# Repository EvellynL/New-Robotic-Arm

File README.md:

# 🦾Novo Braço Robótico - STEM CRIAR

O Novo Braço Robótico – STEM CRIAR é um projeto desenvolvido no âmbito do projeto STEM CRIAR. Este repositório reúne os códigos-fonte, bibliotecas, configurações e demais arquivos utilizados no desenvolvimento e controle do braço robótico.

## 💻Programação

Toda programação foi desenvolvida em C++ utilizando a plataforma **Visual Studio Code** juntamente com a extensão **PlatformIO (3.3.4)**. O projeto foi criado utilizando servos inteligentes da **Hiwonder** que contam driver, motor e circuito de controle de barramento. Os usuários podem enviar comandos específicos ao servomotor — com base no protocolo de comunicação fornecido pela nossa empresa — para controlar a rotação, ler informações do dispositivo ou alternar para o modo de motor de passo. Cada servomotor possui três interfaces, permitindo a conexão em cascata.

Link com mais informações sobre os servos inteligentes: https://drive.google.com/drive/folders/1yaZ8iRYgWncdHPopioo7OYuHoGhrMxCi?hl=pt-br <br>
Manual de configuração dos servos LX-15D também se encontra em: [eletronica](eletronica/LX_15D_Bus_Servo_User_Manual.pdf)

## ⚡Eletrônica

### 📍Componentes utilizados: 
- Servos LX-15D
- Serial Bus Servo Controller LBSC - V1.5
- ESP32 WROOM 32D
- Regulador de Tensão LM2596 ajustável com display
- Bateria 9v

### 📍Diagrama Elétrico: 

Link sobre informações da placa Serial Bus Servo Controller LBSC - V1.5 e configurar os ID's dos servos: https://docs.hiwonder.com/projects/Bus-Servo-Controller/en/latest/docs/1.Bus_Servo_Controller_User_Manual.html

## ⚙️Mecânica

Toda estrutura mecânica foi modelada e desenvolvida utilizando o software Inventor Autodesk na versão 2027 e se encontram na pasta: [Mecânica](mecanica/partes_ipt)

A fabricação das peças foram feitas nas impressoras 3D da Bambu Lab do modelo P1S utilizando filemanto PLA.

MAIS DETALHES EM ANDAMENTO....🚧🚧🚧

## ⚠️Observações:
- A tensão de operação dos Servos LX-15D está entre 6v - 8.4v. Valores menores impediram o funcionamento e valores maiores danificaram o componente.
- O ESP32 não controla os servos diretamente; ele se comunica com a placa Serial Bus Servo Controller por meio de uma interface serial UART. Portanto, a interface UART utilizada para a comunicação com a placa **não deve ser compartilhada com o Monitor Serial**, sendo recomendável utilizar interfaces seriais distintas para cada finalidade.
- Os Servos só funcionaram se estiverem pré-definidos com o seus ID's.
- Ao configurar os IDs dos servos utilizando o software da HiWonder, é possível que, em algumas placas controladoras, a porta de comunicação não seja identificada como uma porta COM no Windows, mas apareça no Gerenciador de Dispositivos como um dispositivo na categoria Human Interface Devices (HID). Isso ocorre porque, nesse caso, a comunicação com a placa é estabelecida por meio da **interface Wire**. Para verificar se a conexão foi reconhecida corretamente, basta consultar o status de “Wire Connect” no software da HiWonder.

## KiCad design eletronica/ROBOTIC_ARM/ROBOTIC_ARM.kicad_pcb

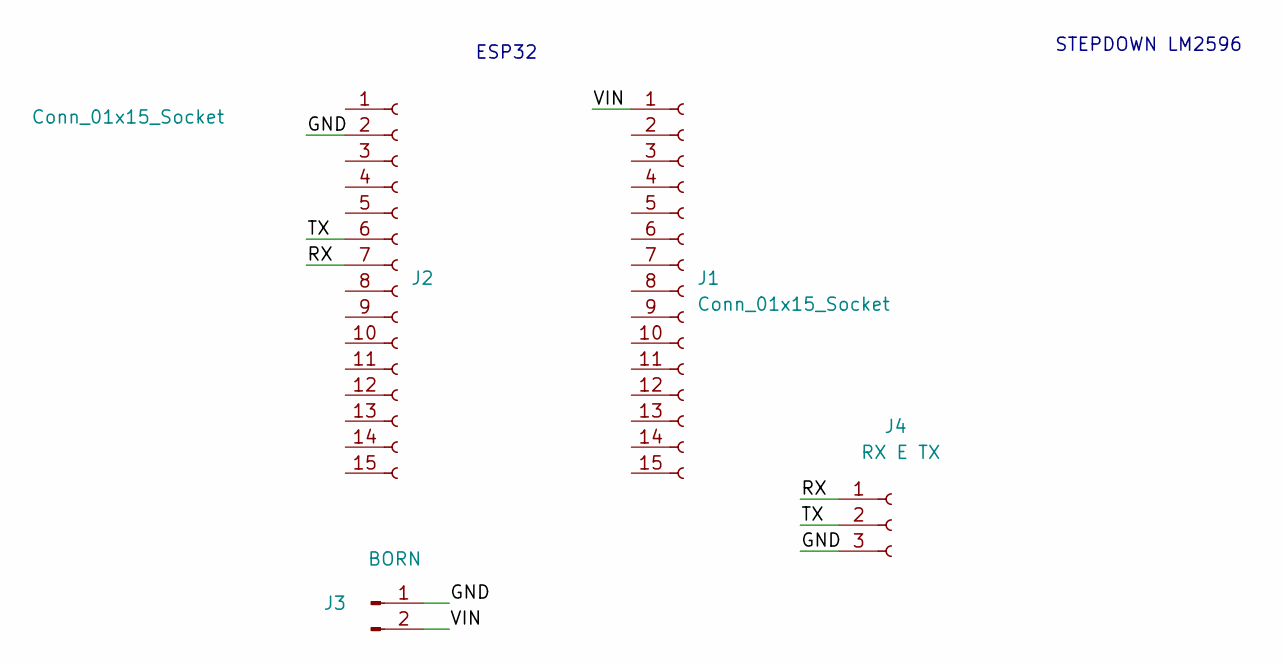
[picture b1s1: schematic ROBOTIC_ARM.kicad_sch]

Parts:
J1, J2: Conn_01x15_Socket; PinSocket_1x15_P2.54mm_Vertical
J3: BORN; TerminalBlock_Phoenix_MKDS-1,5-2_1x02_P5.00mm_Horizontal
J4: RX E TX; PinSocket_1x03_P2.54mm_Vertical

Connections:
/GND: J2.2, J3.1, J4.3
/RX: J2.7, J4.1
/TX: J2.6, J4.2
/VIN: J1.1 (Pin_1_1), J3.2

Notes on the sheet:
STEPDOWN LM2596
ESP32

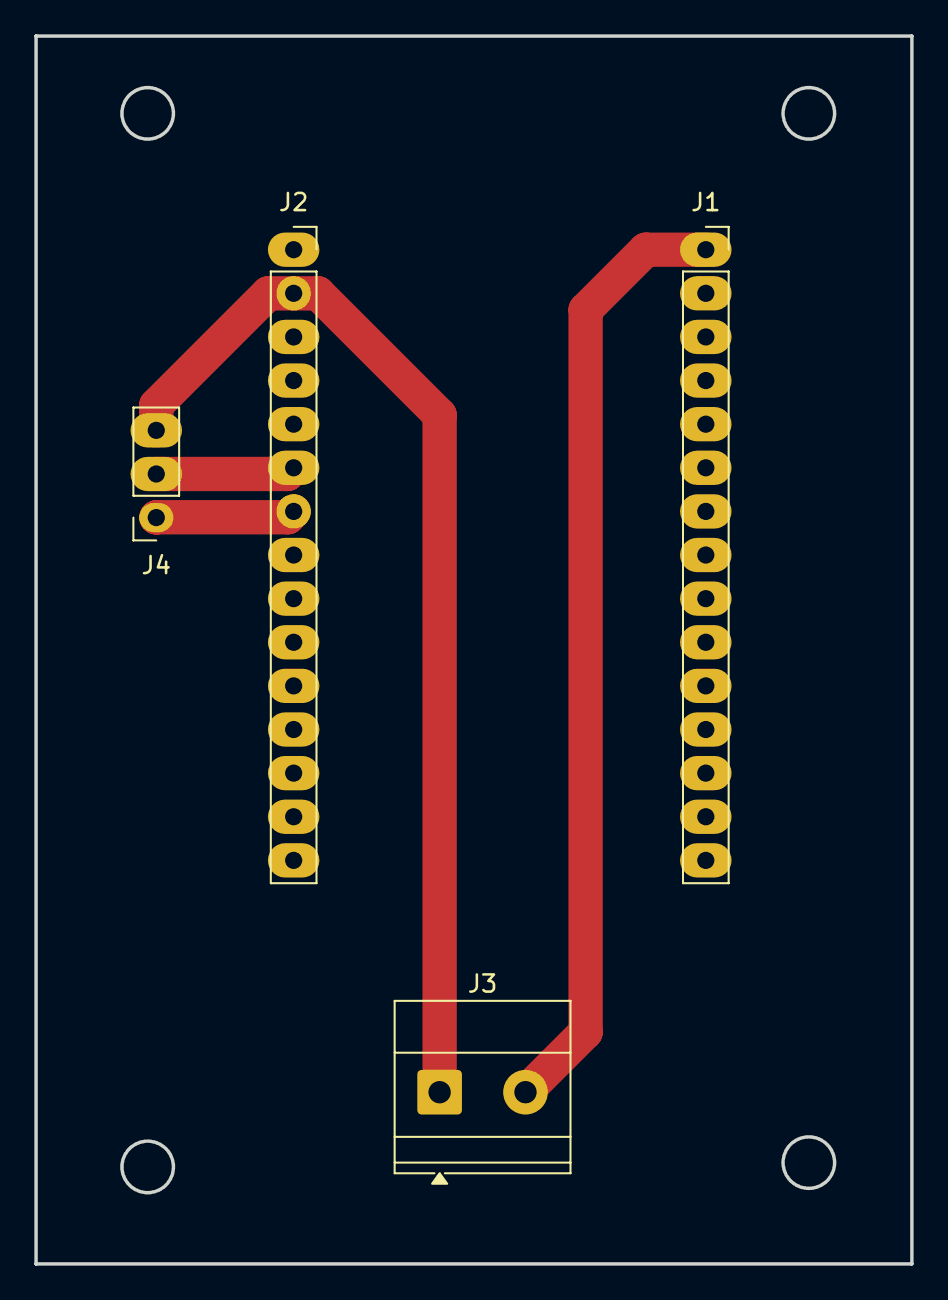
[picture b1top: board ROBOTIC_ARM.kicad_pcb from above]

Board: 2 copper layers, 51.0 x 71.5 mm, 4 parts (0 on the bottom side), 4 nets.
